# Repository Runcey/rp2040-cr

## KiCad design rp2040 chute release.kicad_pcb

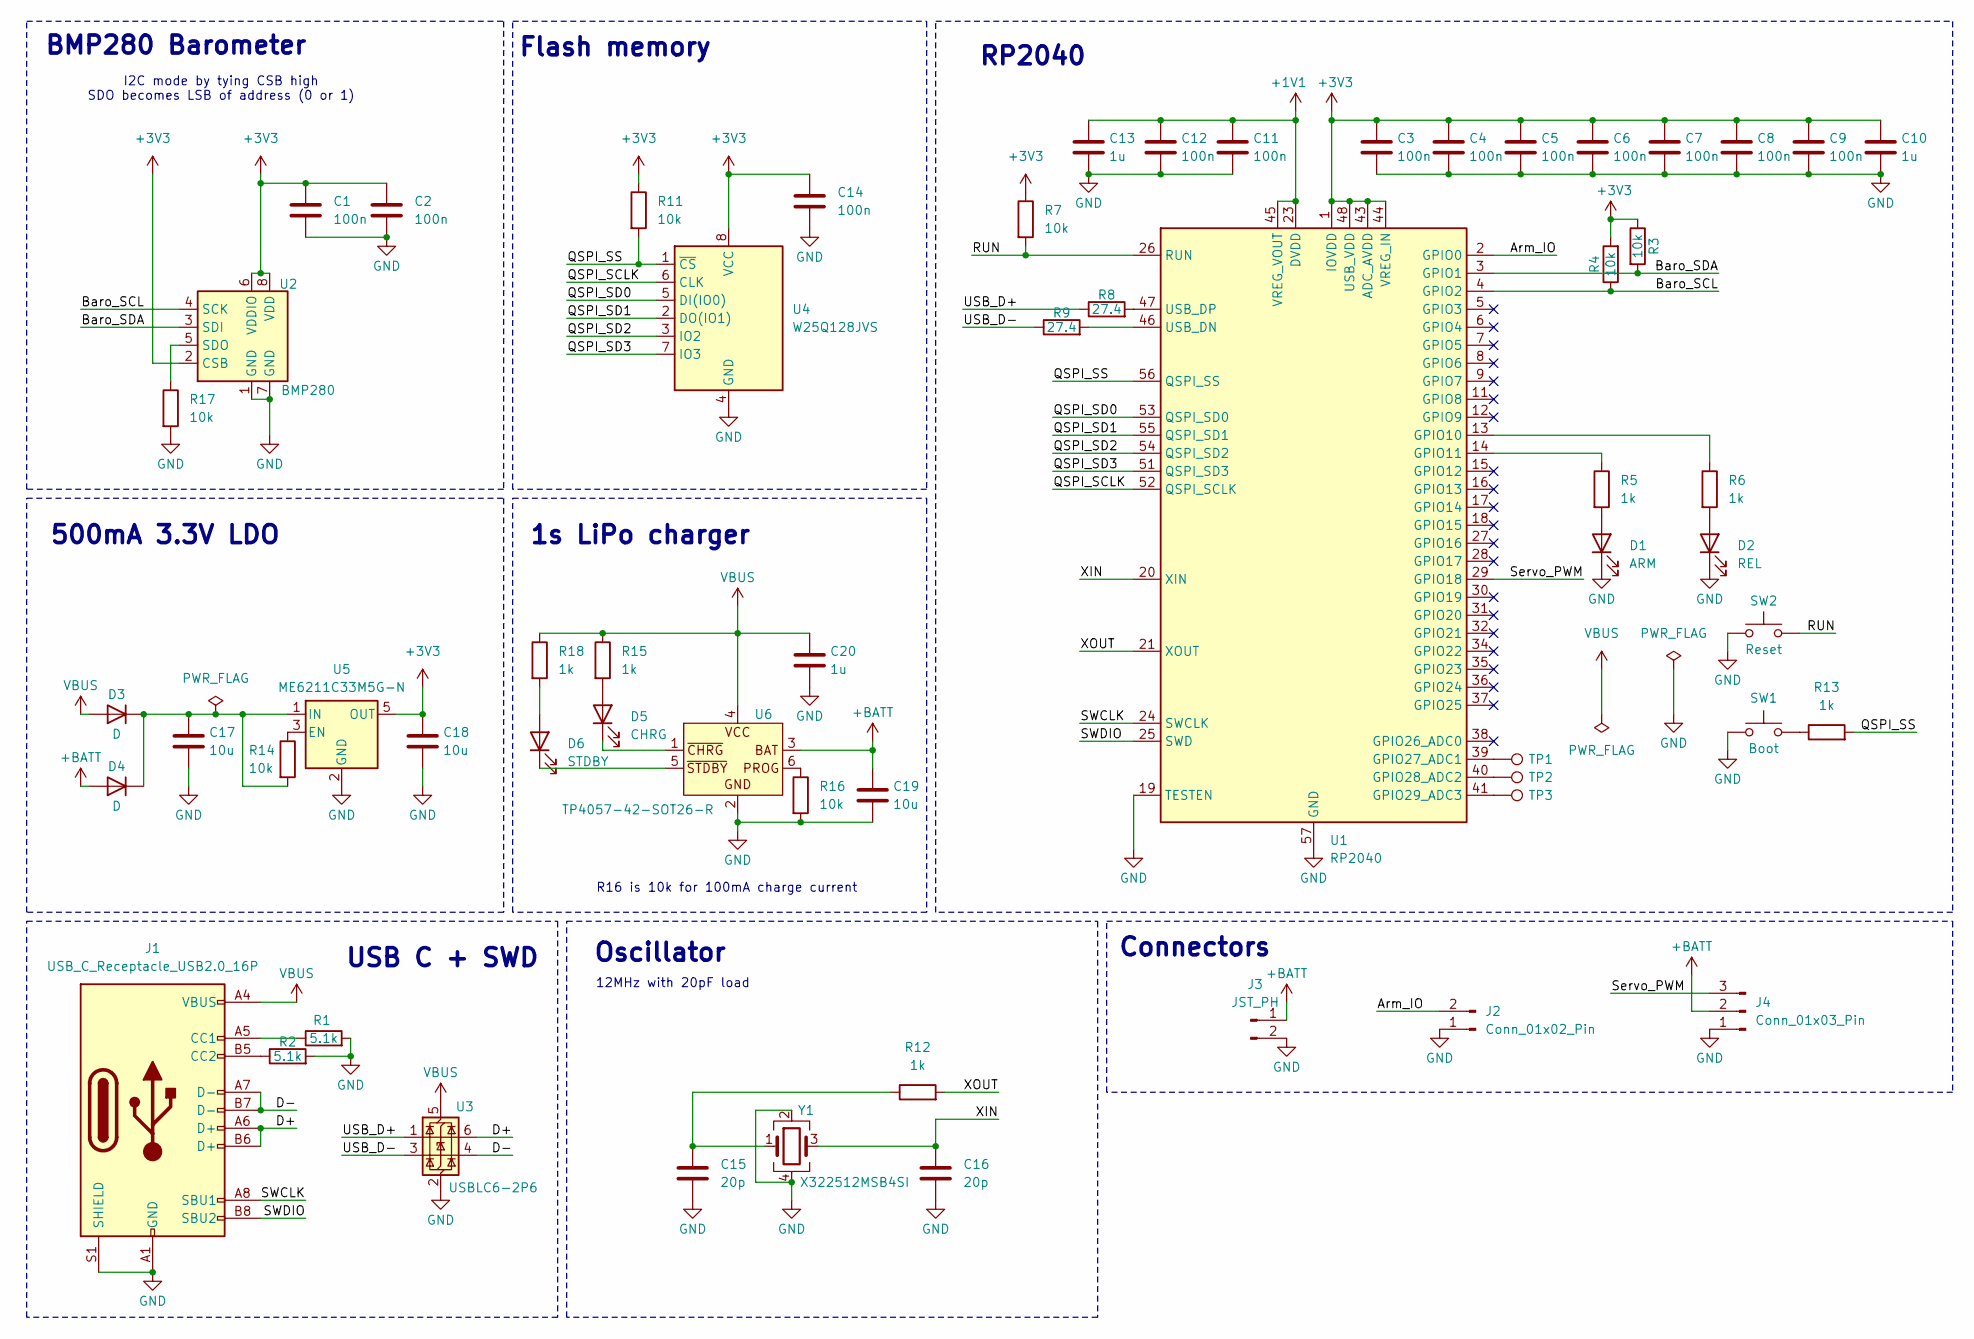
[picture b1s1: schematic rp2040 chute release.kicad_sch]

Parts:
C1, C2, C3, C4, C5, C6, C7, C8, C9, C11, C12, C14: 100n; C_0402_1005Metric_Pad0.74x0.62mm_HandSolder
C10, C13, C20: 1u; C_0402_1005Metric_Pad0.74x0.62mm_HandSolder
C15, C16: 20p; C_0402_1005Metric_Pad0.74x0.62mm_HandSolder
C17, C18, C19: 10u; C_0603_1608Metric_Pad1.08x0.95mm_HandSolder
D1: ARM; LED_0603_1608Metric_Pad1.05x0.95mm_HandSolder
D2: REL; LED_0603_1608Metric_Pad1.05x0.95mm_HandSolder
D3, D4: D; D_SOD-323_HandSoldering
D5: CHRG; LED_0603_1608Metric_Pad1.05x0.95mm_HandSolder
D6: STDBY; LED_0603_1608Metric_Pad1.05x0.95mm_HandSolder
J1: USB_C_Receptacle_USB2.0_16P; USB_C_Receptacle_GCT_USB4105-xx-A_16P_TopMnt_Horizontal
J2: Conn_01x02_Pin; PinHeader_1x02_P2.54mm_Vertical
J3: JST_PH; JST_PH_S2B-PH-SM4-TB_1x02-1MP_P2.00mm_Horizontal
J4: Conn_01x03_Pin; PinHeader_1x03_P2.54mm_Vertical
R1, R2: 5.1k; R_0603_1608Metric_Pad0.98x0.95mm_HandSolder
R3, R4, R7, R11, R14, R16, R17: 10k; R_0603_1608Metric_Pad0.98x0.95mm_HandSolder
R5, R6, R12, R13, R15, R18: 1k; R_0603_1608Metric_Pad0.98x0.95mm_HandSolder
R8, R9: 27.4; R_0603_1608Metric_Pad0.98x0.95mm_HandSolder
SW1: Boot; SW_SPST_B3U-1000P
SW2: Reset; SW_SPST_B3U-1000P
TP1, TP2, TP3: TestPoint; TestPoint_Pad_D1.0mm
U1: RP2040; QFN-56-1EP_7x7mm_P0.4mm_EP3.2x3.2mm
U2: BMP280; Bosch_LGA-8_2x2.5mm_P0.65mm_ClockwisePinNumbering
U3: USBLC6-2P6; SOT-666
U4: W25Q128JVS; SOIC-8_5.23x5.23mm_P1.27mm
U5: ME6211C33M5G-N; SOT-23-5
U6: TP4057-42-SOT26-R; SOT-23-6
Y1: X322512MSB4SI; Crystal_SMD_3225-4Pin_3.2x2.5mm

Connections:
+1V1: C11.1, C12.1, C13.1, U1.23 (DVDD), U1.45 (VREG_VOUT), U1.50 (DVDD)
+3V3: C1.1, C2.1, C3.1, C4.1, C5.1, C6.1, C7.1, C8.1, C9.1, C10.1, C14.1, C18.1, R3.1, R4.2, R7.1, R11.1, U1.1 (IOVDD), U1.10 (IOVDD), U1.22 (IOVDD), U1.33 (IOVDD), U1.42 (IOVDD), U1.43 (ADC_AVDD), U1.44 (VREG_IN), U1.48 (USB_VDD), U1.49 (IOVDD), U2.2 (CSB), U2.6 (VDDIO), U2.8 (VDD), U4.8 (VCC), U5.5 (OUT)
+BATT: C19.1, D4.2 (A), J3.1, J4.2, U6.3
/Arm_IO: J2.2, U1.2 (GPIO0)
/Baro_SCL: R4.1, U1.4 (GPIO2), U2.4 (SCK)
/Baro_SDA: R3.2, U1.3 (GPIO1), U2.3 (SDI)
/D+: J1.A6 (D+), J1.B6 (D+), U3.6 (I/O1)
/D-: J1.A7 (D-), J1.B7 (D-), U3.4 (I/O2)
/QSPI_SCLK: U1.52 (QSPI_SCLK), U4.6 (CLK)
/QSPI_SD0: U1.53 (QSPI_SD0), U4.5 (DI(IO0))
/QSPI_SD1: U1.55 (QSPI_SD1), U4.2 (DO(IO1))
/QSPI_SD2: U1.54 (QSPI_SD2), U4.3 (IO2)
/QSPI_SD3: U1.51 (QSPI_SD3), U4.7 (IO3)
/QSPI_SS: R11.2, R13.2, U1.56 (QSPI_SS), U4.1 (~CS)
/RUN: R7.2, SW2.2, U1.26 (RUN)
/SWCLK: J1.A8 (SBU1), U1.24 (SWCLK)
/SWDIO: J1.B8 (SBU2), U1.25 (SWD)
/Servo_PWM: J4.3, U1.29 (GPIO18)
/USB_D+: R8.1, U3.1 (I/O1)
/USB_D-: R9.1, U3.3 (I/O2)
/XIN: C16.1, U1.20 (XIN), Y1.3
/XOUT: R12.2, U1.21 (XOUT)
GND: C1.2, C2.2, C3.2, C4.2, C5.2, C6.2, C7.2, C8.2, C9.2, C10.2, C11.2, C12.2, C13.2, C14.2, C15.2, C16.2, C17.2, C18.2, C19.2, C20.2, D1.1 (K), D2.1 (K), J1.A1 (GND), J1.A12 (GND), J1.B1 (GND), J1.B12 (GND), J1.S1 (SHIELD), J2.1, J3.2, J4.1, R1.2, R2.2, R16.2, R17.2, SW1.1, SW2.1, U1.19 (TESTEN), U1.57 (GND), U2.1 (GND), U2.7 (GND), U3.2 (GND), U4.4 (GND), U5.2 (GND), U6.2, Y1.2, Y1.4
unnamed: C15.1, R12.1, Y1.1
unnamed: D1.2 (A), R5.2
unnamed: D2.2 (A), R6.2
unnamed: C17.1, D3.1 (K), D4.1 (K), R14.2, U5.1 (IN)
unnamed: D5.2 (A), R15.2
unnamed: D5.1 (K), U6.1
unnamed: D6.2 (A), R18.2
unnamed: D6.1 (K), U6.5
unnamed: J1.A5 (CC1), R1.1
unnamed: J1.B5 (CC2), R2.1
unnamed: R13.1, SW1.2
unnamed: R16.1, U6.6
unnamed: R6.1, U1.13 (GPIO10)
unnamed: R5.1, U1.14 (GPIO11)
unnamed: TP1.1, U1.39 (GPIO27_ADC1)
unnamed: TP2.1, U1.40 (GPIO28_ADC2)
unnamed: TP3.1, U1.41 (GPIO29_ADC3)
unnamed: R9.2, U1.46 (USB_DN)
unnamed: R8.2, U1.47 (USB_DP)
unnamed: R17.1, U2.5 (SDO)
unnamed: R14.1, U5.3 (EN)
VBUS: C20.1, D3.2 (A), J1.A4 (VBUS), J1.A9 (VBUS), J1.B4 (VBUS), J1.B9 (VBUS), R15.1, R18.1, U3.5 (VBUS), U6.4

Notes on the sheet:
R16 is 10k for 100mA charge current
RP2040
12MHz with 20pF load
500mA 3.3V LDO
Oscillator
1s LiPo charger
USB C + SWD
Flash memory
Connectors
BMP280 Barometer
I2C mode by tying CSB high SDO becomes LSB of address (0 or 1)

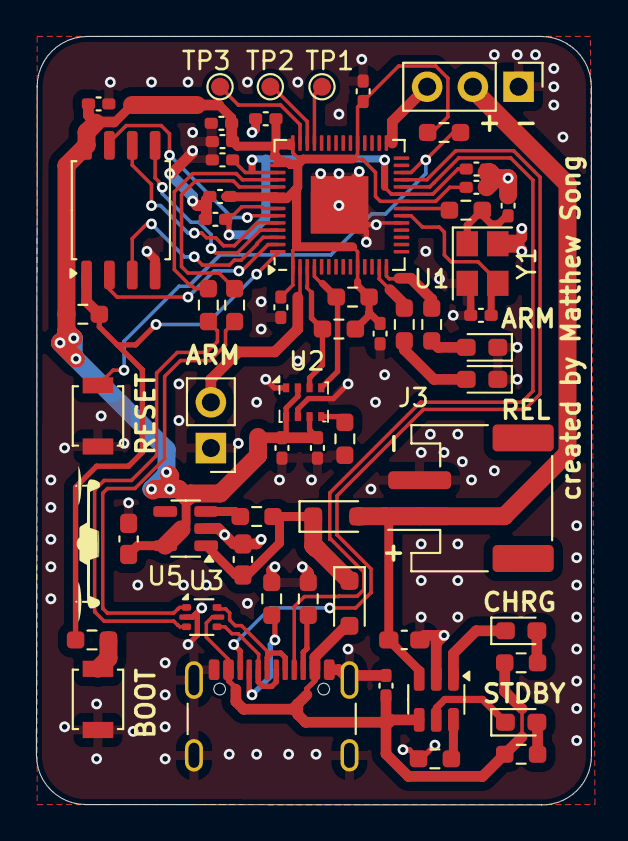
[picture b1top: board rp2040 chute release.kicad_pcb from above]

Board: 2 copper layers, 30.8 x 42.7 mm, 59 parts (0 on the bottom side), 45 nets.

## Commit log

2025-05-10 first push
